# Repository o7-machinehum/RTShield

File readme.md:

# RPI RTShield

The RTSheild is a Raspberry PI hat containing an MCU to serve as a "realtime" companion. The PI is connected to the RP2350 over a UART link, and all sensors are wired into the RP2350 itself. The RP2350 is connected to Arduino compatible headers

## IOs
- 4x Analog output (0-3.3V, 12bit)
- 8x Analog input (0-3.3V, 12bit)
- IO's (3.3V)
- 2x Relays, for dry contacts
- Switches, for config
- LEDs

## Installing
``` bash
git clone https://github.com/o7-machinehum/RTShield
cd RTShield
git submodule update --init --recursive

sudo apt update
sudo apt install -y build-essential cmake ninja-build gcc-arm-none-eabi \
    libnewlib-arm-none-eabi python3-dev python3-pybind11 openocd

sudo raspi-config nonint do_serial_cons 1
sudo raspi-config nonint do_serial_hw 0
sudo usermod -aG dialout "$USER"

make
make flash # This flashes the RP2350

make install

# Reboot once so the serial-console setting and dialout group membership apply.
sudo reboot
```

## Running
The Python API talks to the shield over `/dev/serial0`:

``` python
import rtshield

s = rtshield.Shield("/dev/serial0")
print(s.read_analog_raw(0))
s.write_analog_voltage(0, 1.25)
s.write_digital(2, True)
s.set_led(0, True)
s.set_relay(0, True)
print(s.read_switch(0))
```

## MCU <-> RPI Coms
It's worth mentioning the UART between the MCU and the RPI isn't done very nicely right now. This is to keep things simple. I will eventually do a proper cobs encoding scheme and make things nicer.

## License
The project is licensed under the Creative Commons (4.0 International License) Attribution—Noncommercial—Share Alike license. This allows sharing and adapting material for non-commercial purposes, provided credit is given to the creator and adaptations are shared under the same terms. The material can be used in any format with necessary technical modifications, but no warranties are provided. The license prohibits imposing additional restrictions and ensures the rights are irrevocable as long as the terms are followed.

Basically... If you make boards for yourself: great, make boards for your friends: great, but **please do not sell hundreds on them on Aliexpress**.

Files in `docs/` 3rd party reference material are not covered by this licence.

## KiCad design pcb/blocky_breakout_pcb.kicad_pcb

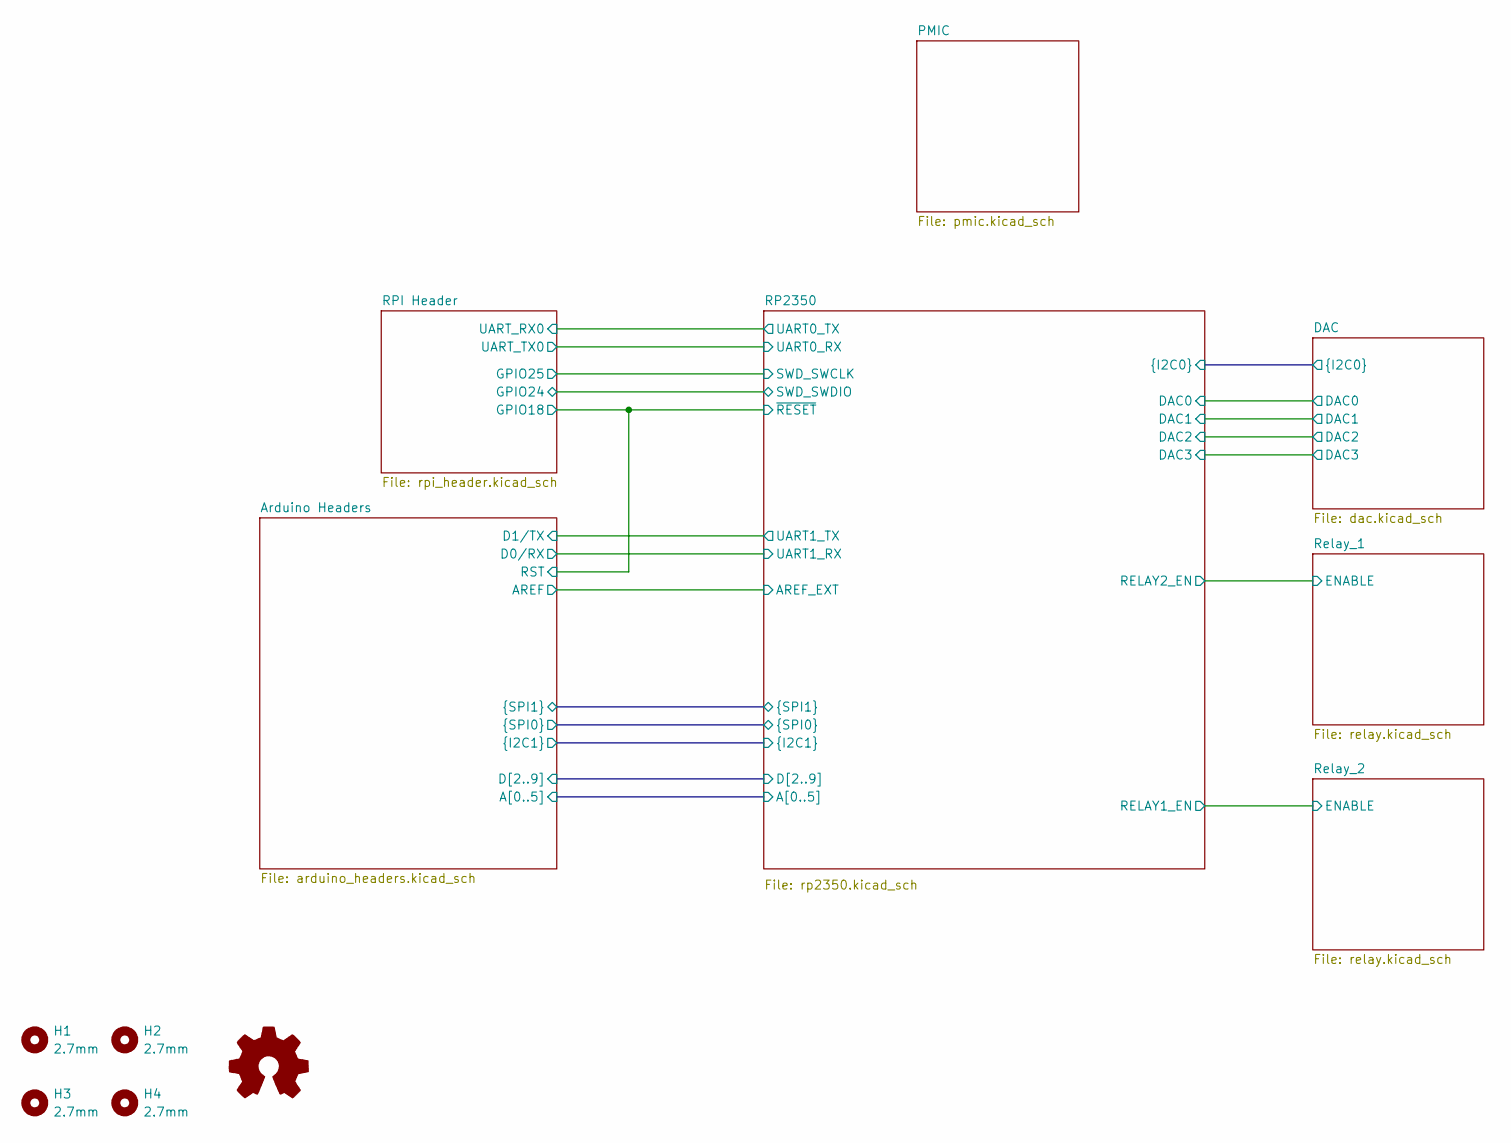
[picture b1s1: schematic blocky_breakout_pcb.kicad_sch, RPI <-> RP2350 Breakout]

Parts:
H1, H2, H3, H4: 2.7mm; MountingHole_2.7mm_M2.5

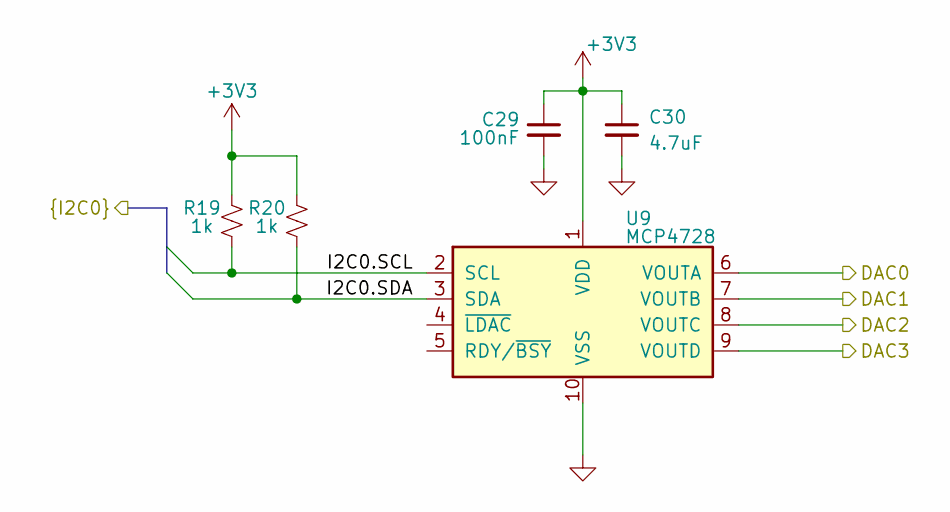
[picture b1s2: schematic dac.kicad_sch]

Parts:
C29: 100nF; C_0402_1005Metric; MPN CL05B104KP5NNNC
C30: 4.7uF; C_0402_1005Metric; MPN JMK105BBJ475MV-F
R19, R20: 1k; R_0402_1005Metric; MPN RC0402FR-131KL
U9: MCP4728; MSOP-10_3x3mm_P0.5mm; MPN MCP4728T-E/UN

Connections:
+3V3: C29.1, C30.1, R19.2, R20.2, U9.1 (VDD); also elsewhere on the board
/DAC/DAC0: U9.6 (VOUTA); also elsewhere on the board
/DAC/DAC1: U9.7 (VOUTB); also elsewhere on the board
/DAC/DAC2: U9.8 (VOUTC); also elsewhere on the board
/DAC/DAC3: U9.9 (VOUTD); also elsewhere on the board
/DAC/I2C0.SCL: R19.1, U9.2 (SCL); also elsewhere on the board
/DAC/I2C0.SDA: R20.1, U9.3 (SDA); also elsewhere on the board
GND: C29.2, C30.2, U9.10 (VSS); also elsewhere on the board

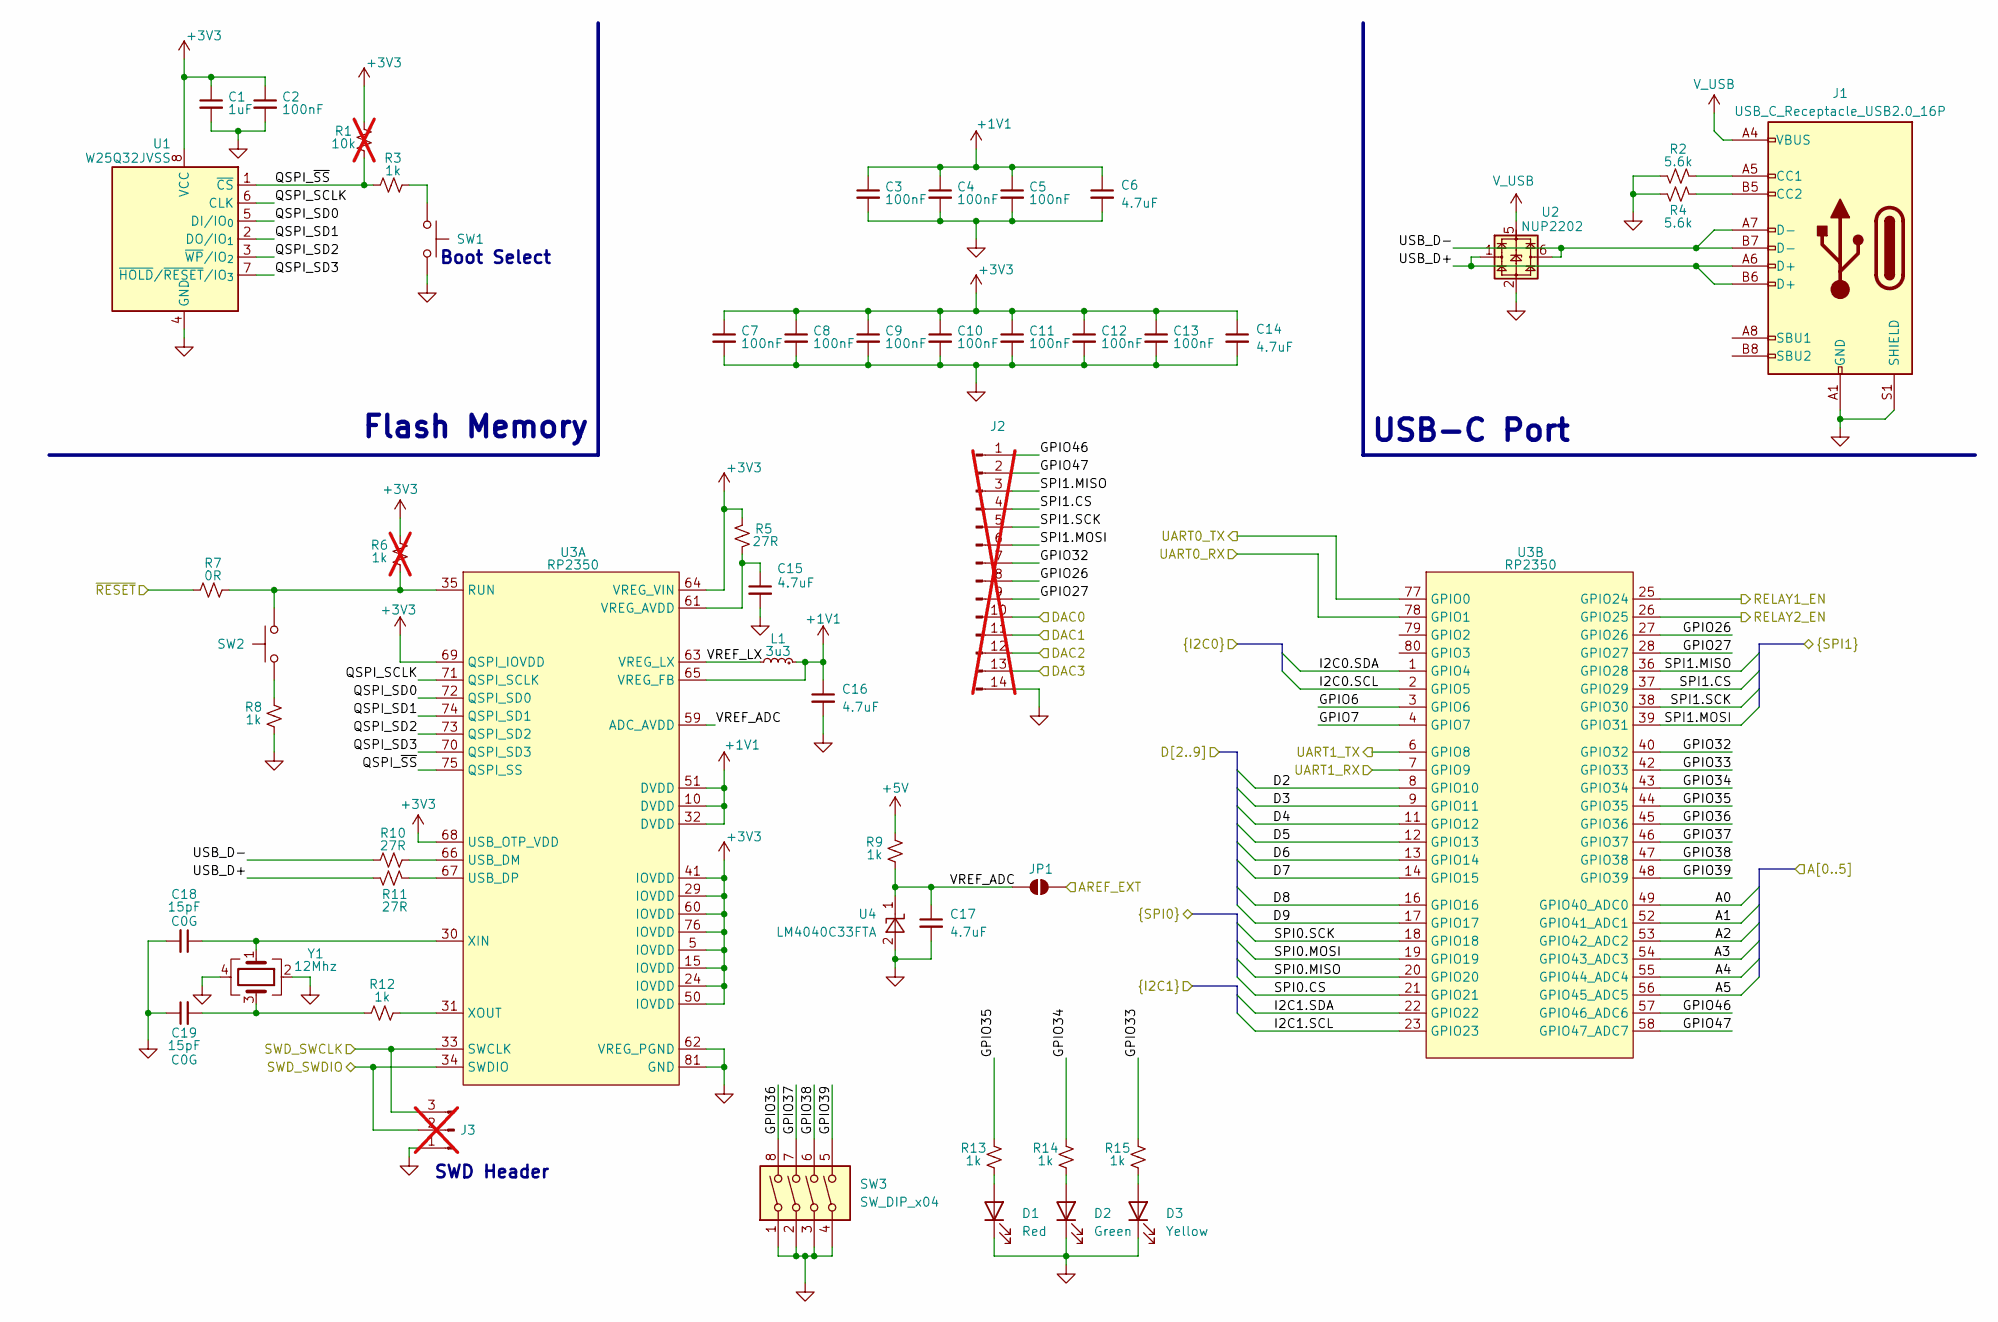
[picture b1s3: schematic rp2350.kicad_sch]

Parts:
C1: 1uF; C_0402_1005Metric; MPN JMK105BJ105KV-F
C2, C3, C4, C5, C7, C8, C9, C10, C11, C12, C13: 100nF; C_0402_1005Metric; MPN CL05B104KP5NNNC
C6, C14, C15, C16, C17: 4.7uF; C_0402_1005Metric; MPN JMK105BBJ475MV-F
C18, C19: 15pF; C_0402_1005Metric; MPN GJM1555C1H150GB01D
D1: Red; LED_0603_1608Metric; MPN LTST-C190KRKT
D2: Green; LED_0603_1608Metric; MPN LTST-C190GKT
D3: Yellow; LED_0603_1608Metric; MPN LTST-C190KSKT
J1: USB_C_Receptacle_USB2.0_16P; USB_C_Receptacle_GCT_USB4105-xx-A_16P_TopMnt_Horizontal; MPN USB4105-GF-A-120
J2: Conn_01x14_Pin; PinHeader_1x14_P2.54mm_Vertical; MPN 77311-101-14LF; not fitted
J3: Conn_01x03_Pin; PinHeader_1x03_P2.54mm_Vertical; not fitted
JP1: SolderJumper_2_Open; SolderJumper-2_P1.3mm_Open_RoundedPad1.0x1.5mm
L1: 3u3; AOTA-B201610S3R3-101-T; MPN AOTA-B201610S3R3-101-T
R1: 10k; R_0402_1005Metric; MPN RC0402FR-1310KL; not fitted
R2, R4: 5.6k; R_0402_1005Metric; MPN RC0402FR-135K6L
R3, R8, R9, R12, R13, R14, R15: 1k; R_0402_1005Metric; MPN RC0402FR-131KL
R5, R10, R11: 27R; R_0402_1005Metric; MPN RC0402FR-1327RL
R6: 1k; R_0402_1005Metric; MPN RC0402FR-131KL; not fitted
R7: 0R; R_0402_1005Metric; MPN RC0402FR-070RL
SW1, SW2: SW_Push; SW_SPST_PTS647_Sx38; MPN PTS647SK38SMTR2 LFS
SW3: SW_DIP_x04; SW_DIP_SPSTx04_Slide_Omron_A6S-410x_W8.9mm_P2.54mm; MPN A6S-4102-PH
U1: W25Q32JVSS; SOIC-8_5.3x5.3mm_P1.27mm; MPN W25Q32JVSSIQ
U2: NUP2202; SOT-363_SC-70-6; MPN NUP2202W1T2G
U3: RP2350; QFN-80-1EP_10x10mm_P0.4mm_EP3.4x3.4mm; MPN RP2350B
U4: LM4040C33FTA; SOT-23; MPN LM4040C33FTA
Y1: 12Mhz; Crystal_SMD_Abracon_ABM8-272-T3-4Pin_3.2x2.5mm; MPN ABM8-272-T3

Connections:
+1V1: C3.1, C4.1, C5.1, C6.1, C16.1, L1.1, U3.10 (DVDD), U3.32 (DVDD), U3.51 (DVDD), U3.65 (VREG_FB); also elsewhere on the board
+3V3: C1.1, C2.1, C7.1, C8.1, C9.1, C10.1, C11.1, C12.1, C13.1, C14.1, R1.2, R5.2, R6.2, U1.8 (VCC), U3.5 (IOVDD), U3.15 (IOVDD), U3.24 (IOVDD), U3.29 (IOVDD), U3.41 (IOVDD), U3.50 (IOVDD), U3.60 (IOVDD), U3.64 (VREG_VIN), U3.68 (USB_OTP_VDD), U3.69 (QSPI_IOVDD), U3.76 (IOVDD); also elsewhere on the board
+5V: R9.2; also elsewhere on the board
/Arduino Headers/A0: U3.49 (GPIO40_ADC0); also elsewhere on the board
/Arduino Headers/A1: U3.52 (GPIO41_ADC1); also elsewhere on the board
/Arduino Headers/A2: U3.53 (GPIO42_ADC2); also elsewhere on the board
/Arduino Headers/A3: U3.54 (GPIO43_ADC3); also elsewhere on the board
/Arduino Headers/A4: U3.55 (GPIO44_ADC4); also elsewhere on the board
/Arduino Headers/A5: U3.56 (GPIO45_ADC5); also elsewhere on the board
/Arduino Headers/AREF: JP1.2 (B); also elsewhere on the board
/Arduino Headers/D0/RX: U3.7 (GPIO9); also elsewhere on the board
/Arduino Headers/D1/TX: U3.6 (GPIO8); also elsewhere on the board
/Arduino Headers/D2: U3.8 (GPIO10); also elsewhere on the board
/Arduino Headers/D3: U3.9 (GPIO11); also elsewhere on the board
/Arduino Headers/D4: U3.11 (GPIO12); also elsewhere on the board
/Arduino Headers/D5: U3.12 (GPIO13); also elsewhere on the board
/Arduino Headers/D6: U3.13 (GPIO14); also elsewhere on the board
/Arduino Headers/D7: U3.14 (GPIO15); also elsewhere on the board
/Arduino Headers/D8: U3.16 (GPIO16); also elsewhere on the board
/Arduino Headers/D9: U3.17 (GPIO17); also elsewhere on the board
/Arduino Headers/I2C1.SCL: U3.23 (GPIO23); also elsewhere on the board
/Arduino Headers/I2C1.SDA: U3.22 (GPIO22); also elsewhere on the board
/Arduino Headers/RST: R7.1; also elsewhere on the board
/Arduino Headers/SPI0.CS: U3.21 (GPIO21); also elsewhere on the board
/Arduino Headers/SPI0.MISO: U3.20 (GPIO20); also elsewhere on the board
/Arduino Headers/SPI0.MOSI: U3.19 (GPIO19); also elsewhere on the board
/Arduino Headers/SPI0.SCK: U3.18 (GPIO18); also elsewhere on the board
/Arduino Headers/SPI1.CS: J2.4, U3.37 (GPIO29)
/Arduino Headers/SPI1.MISO: J2.3, U3.36 (GPIO28); also elsewhere on the board
/Arduino Headers/SPI1.MOSI: J2.6, U3.39 (GPIO31); also elsewhere on the board
/Arduino Headers/SPI1.SCK: J2.5, U3.38 (GPIO30); also elsewhere on the board
/DAC/DAC0: J2.10; also elsewhere on the board
/DAC/DAC1: J2.11; also elsewhere on the board
/DAC/DAC2: J2.12; also elsewhere on the board
/DAC/DAC3: J2.13; also elsewhere on the board
/DAC/I2C0.SCL: U3.2 (GPIO5); also elsewhere on the board
/DAC/I2C0.SDA: U3.1 (GPIO4); also elsewhere on the board
/RP2350/GPIO6: U3.3 (GPIO6)
/RP2350/GPIO7: U3.4 (GPIO7)
/RP2350/GPIO26: J2.8, U3.27 (GPIO26)
/RP2350/GPIO27: J2.9, U3.28 (GPIO27)
/RP2350/GPIO32: J2.7, U3.40 (GPIO32)
/RP2350/GPIO33: R15.2, U3.42 (GPIO33)
/RP2350/GPIO34: R14.2, U3.43 (GPIO34)
/RP2350/GPIO35: R13.2, U3.44 (GPIO35)
/RP2350/GPIO36: SW3.8, U3.45 (GPIO36)
/RP2350/GPIO37: SW3.7, U3.46 (GPIO37)
/RP2350/GPIO38: SW3.6, U3.47 (GPIO38)
/RP2350/GPIO39: SW3.5, U3.48 (GPIO39)
/RP2350/GPIO46: J2.1, U3.57 (GPIO46_ADC6)
/RP2350/GPIO47: J2.2, U3.58 (GPIO47_ADC7)
/RP2350/QSPI_SCLK: U1.6 (CLK), U3.71 (QSPI_SCLK)
/RP2350/QSPI_SD0: U1.5 (DI/IO_{0}), U3.72 (QSPI_SD0)
/RP2350/QSPI_SD1: U1.2 (DO/IO_{1}), U3.74 (QSPI_SD1)
/RP2350/QSPI_SD2: U1.3 (~WP/IO_{2}), U3.73 (QSPI_SD2)
/RP2350/QSPI_SD3: U1.7 (~HOLD/~RESET/IO_{3}), U3.70 (QSPI_SD3)
/RP2350/QSPI_~SS: R1.1, R3.1, U1.1 (~CS), U3.75 (QSPI_SS)
/RP2350/RELAY1_EN: U3.25 (GPIO24); also elsewhere on the board
/RP2350/RELAY2_EN: U3.26 (GPIO25); also elsewhere on the board
/RP2350/SWD_SWCLK: J3.3, U3.33 (SWCLK); also elsewhere on the board
/RP2350/SWD_SWDIO: J3.2, U3.34 (SWDIO); also elsewhere on the board
/RP2350/UART0_RX: U3.78 (GPIO1); also elsewhere on the board
/RP2350/UART0_TX: U3.77 (GPIO0); also elsewhere on the board
/RP2350/USB_D+: J1.A6 (D+), J1.B6 (D+), R11.1, U2.1
/RP2350/USB_D-: J1.A7 (D-), J1.B7 (D-), R10.1, U2.6
/RP2350/VREF_ADC: C17.1, JP1.1 (A), R9.1, U3.59 (ADC_AVDD), U4.1 (K)
/RP2350/VREF_LX: L1.2, U3.63 (VREG_LX)
GND: C1.2, C2.2, C3.2, C4.2, C5.2, C6.2, C7.2, C8.2, C9.2, C10.2, C11.2, C12.2, C13.2, C14.2, C15.2, C16.2, C17.2, C18.2, C19.1, D1.1 (K), D2.1 (K), D3.1 (K), J1.A1 (GND), J1.A12 (GND), J1.B1 (GND), J1.B12 (GND), J1.S1 (SHIELD), J2.14, J3.1, R2.2, R4.1, R8.1, SW1.2, SW3.1, SW3.2, SW3.3, SW3.4, U1.4 (GND), U2.2, U3.62 (VREG_PGND), U3.81 (GND), U4.2 (A), Y1.2, Y1.4; also elsewhere on the board
unnamed: C19.2, R12.1, Y1.3
unnamed: D1.2 (A), R13.1
unnamed: D2.2 (A), R14.1
unnamed: D3.2 (A), R15.1
unnamed: J1.A5 (CC1), R2.1
unnamed: J1.B5 (CC2), R4.2
unnamed: R3.2, SW1.1
unnamed: R8.2, SW2.1
unnamed: R6.1, R7.2, SW2.2, U3.35 (RUN)
unnamed: R10.2, U3.66 (USB_DM)
unnamed: R11.2, U3.67 (USB_DP)
unnamed: C15.1, R5.1, U3.61 (VREG_AVDD)
unnamed: C18.1, U3.30 (XIN), Y1.1
unnamed: R12.2, U3.31 (XOUT)
V_USB: J1.A4 (VBUS), J1.A9 (VBUS), J1.B4 (VBUS), J1.B9 (VBUS), U2.5; also elsewhere on the board

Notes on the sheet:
SWD Header
Flash Memory
Boot Select
USB-C Port

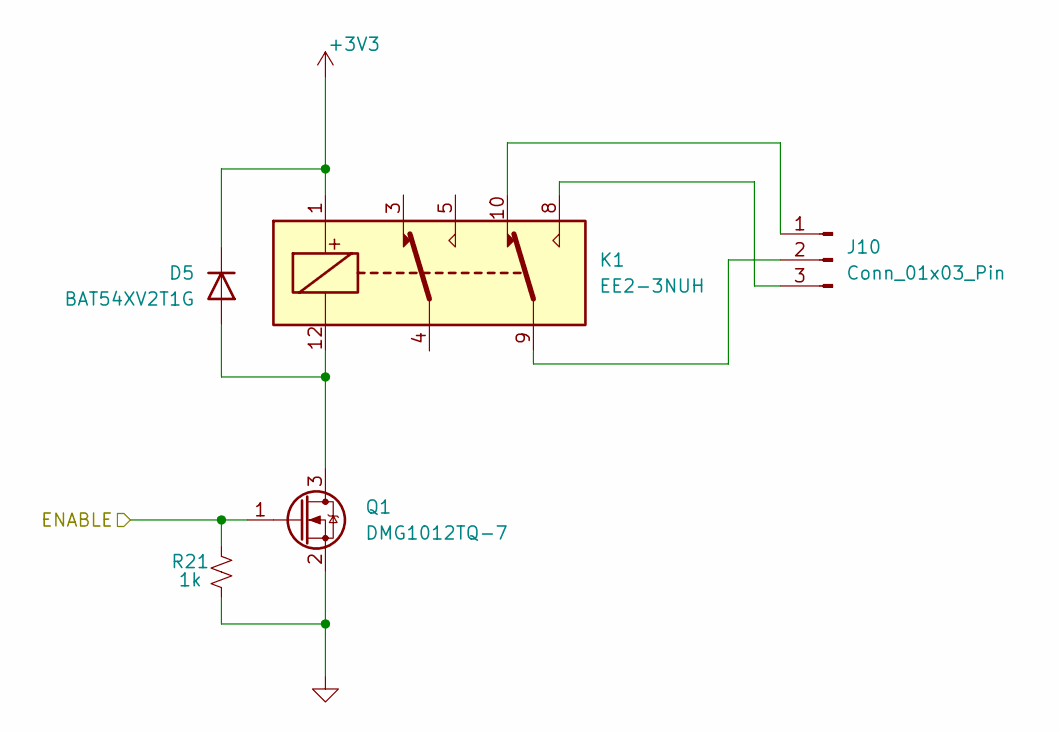
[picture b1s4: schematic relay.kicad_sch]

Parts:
D5: BAT54XV2T1G; D_SOD-523; MPN BAT54XV2T1G
J10: Conn_01x03_Pin; JST_XH_S3B-XH-A-1_1x03_P2.50mm_Horizontal; MPN S3B-XH-A-1
K1: EE2-3NUH; Relay_DPDT_Kemet_EE2_NUH
Q1: DMG1012TQ-7; SOT-523; MPN DMG1012TQ-7
R21: 1k; R_0402_1005Metric; MPN RC0402FR-131KL

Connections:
+3V3: D5.1 (K), K1.1; also elsewhere on the board
/RP2350/RELAY2_EN: Q1.1 (G), R21.1; also elsewhere on the board
GND: Q1.2 (S), R21.2; also elsewhere on the board
unnamed: D5.2 (A), K1.12, Q1.3 (D)
unnamed: J10.1, K1.10
unnamed: J10.2, K1.9
unnamed: J10.3, K1.8

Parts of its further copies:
D6: BAT54XV2T1G; D_SOD-523; MPN BAT54XV2T1G
J11: Conn_01x03_Pin; JST_XH_S3B-XH-A-1_1x03_P2.50mm_Horizontal; MPN S3B-XH-A-1
Q2: DMG1012TQ-7; SOT-523; MPN DMG1012TQ-7
R22: 1k; R_0402_1005Metric; MPN RC0402FR-131KL

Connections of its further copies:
+3V3: D6.1 (K); also elsewhere on the board
/RP2350/RELAY1_EN: Q2.1 (G), R22.1; also elsewhere on the board
GND: Q2.2 (S), R22.2; also elsewhere on the board
unnamed 75: D6.2 (A), Q2.3 (D); also elsewhere on the board
unnamed 81: J11.1; also elsewhere on the board
unnamed 82: J11.2; also elsewhere on the board
unnamed 83: J11.3; also elsewhere on the board

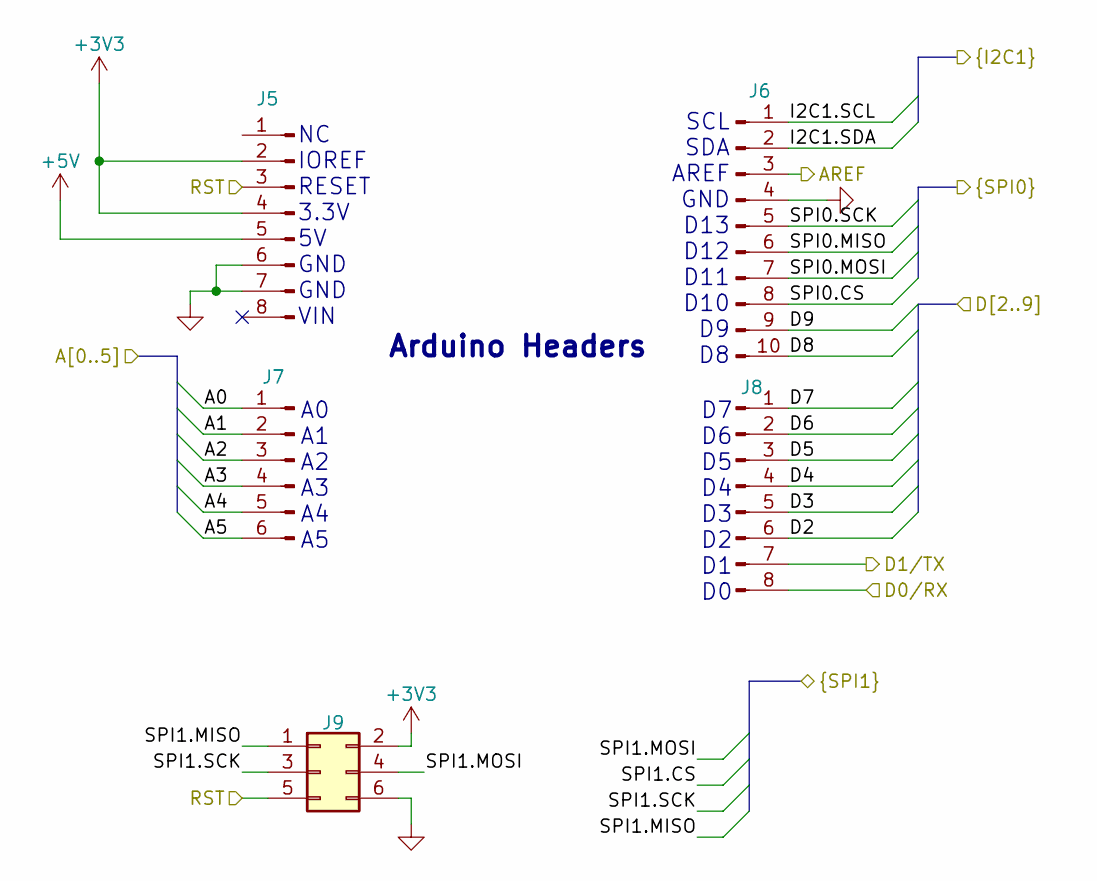
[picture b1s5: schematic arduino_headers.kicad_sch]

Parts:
J5, J8: Conn_01x08_Pin; PinSocket_1x08_P2.54mm_Vertical_SMD_Pin1Left; MPN NPTC081KFXC-RC
J6: Conn_01x10_Pin; PinSocket_1x10_P2.54mm_Vertical_SMD_Pin1Left; MPN NPTC101KFXC-RC
J7: Conn_01x06_Pin; PinSocket_1x06_P2.54mm_Vertical_SMD_Pin1Left; MPN NPTC061KFXC-RC
J9: Conn_02x03_Odd_Even; PinHeader_2x03_P2.54mm_Vertical; MPN 67997-206HLF

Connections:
+3V3: J5.2, J5.4, J9.2; also elsewhere on the board
+5V: J5.5; also elsewhere on the board
/Arduino Headers/A0: J7.1; also elsewhere on the board
/Arduino Headers/A1: J7.2; also elsewhere on the board
/Arduino Headers/A2: J7.3; also elsewhere on the board
/Arduino Headers/A3: J7.4; also elsewhere on the board
/Arduino Headers/A4: J7.5; also elsewhere on the board
/Arduino Headers/A5: J7.6; also elsewhere on the board
/Arduino Headers/AREF: J6.3; also elsewhere on the board
/Arduino Headers/D0/RX: J8.8; also elsewhere on the board
/Arduino Headers/D1/TX: J8.7; also elsewhere on the board
/Arduino Headers/D2: J8.6; also elsewhere on the board
/Arduino Headers/D3: J8.5; also elsewhere on the board
/Arduino Headers/D4: J8.4; also elsewhere on the board
/Arduino Headers/D5: J8.3; also elsewhere on the board
/Arduino Headers/D6: J8.2; also elsewhere on the board
/Arduino Headers/D7: J8.1; also elsewhere on the board
/Arduino Headers/D8: J6.10; also elsewhere on the board
/Arduino Headers/D9: J6.9; also elsewhere on the board
/Arduino Headers/I2C1.SCL: J6.1; also elsewhere on the board
/Arduino Headers/I2C1.SDA: J6.2; also elsewhere on the board
/Arduino Headers/RST: J5.3, J9.5; also elsewhere on the board
/Arduino Headers/SPI0.CS: J6.8; also elsewhere on the board
/Arduino Headers/SPI0.MISO: J6.6; also elsewhere on the board
/Arduino Headers/SPI0.MOSI: J6.7; also elsewhere on the board
/Arduino Headers/SPI0.SCK: J6.5; also elsewhere on the board
/Arduino Headers/SPI1.MISO: J9.1; also elsewhere on the board
/Arduino Headers/SPI1.MOSI: J9.4; also elsewhere on the board
/Arduino Headers/SPI1.SCK: J9.3; also elsewhere on the board
GND: J5.6, J5.7, J6.4, J9.6; also elsewhere on the board

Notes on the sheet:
NC IOREF RESET 3.3V 5V GND GND VIN
D7 D6 D5 D4 D3 D2 D1 D0
SCL SDA AREF GND D13 D12 D11 D10 D9 D8
Arduino Headers
A0 A1 A2 A3 A4 A5

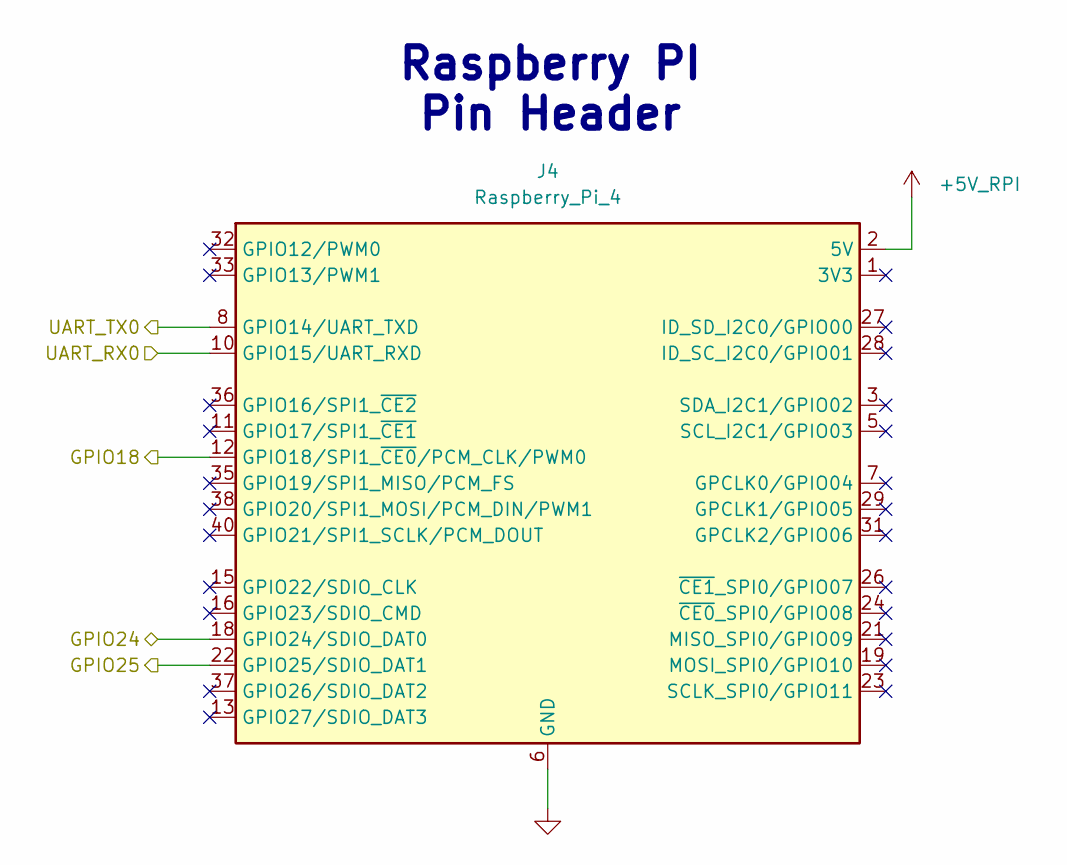
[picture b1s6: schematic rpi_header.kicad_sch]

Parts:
J4: Raspberry_Pi_4; PinSocket_2x20_P2.54mm_Vertical_SMD; MPN NPTC202KFMS-RC

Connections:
+5V_RPI: J4.2 (5V), J4.4 (5V); also elsewhere on the board
/Arduino Headers/RST: J4.12 (GPIO18/SPI1_~CE0/PCM_CLK/PWM0); also elsewhere on the board
/RP2350/SWD_SWCLK: J4.22 (GPIO25/SDIO_DAT1); also elsewhere on the board
/RP2350/SWD_SWDIO: J4.18 (GPIO24/SDIO_DAT0); also elsewhere on the board
/RP2350/UART0_RX: J4.8 (GPIO14/UART_TXD); also elsewhere on the board
/RP2350/UART0_TX: J4.10 (GPIO15/UART_RXD); also elsewhere on the board
GND: J4.6 (GND), J4.9 (GND), J4.14 (GND), J4.20 (GND), J4.25 (GND), J4.30 (GND), J4.34 (GND), J4.39 (GND); also elsewhere on the board

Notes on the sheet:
Raspberry PI Pin Header

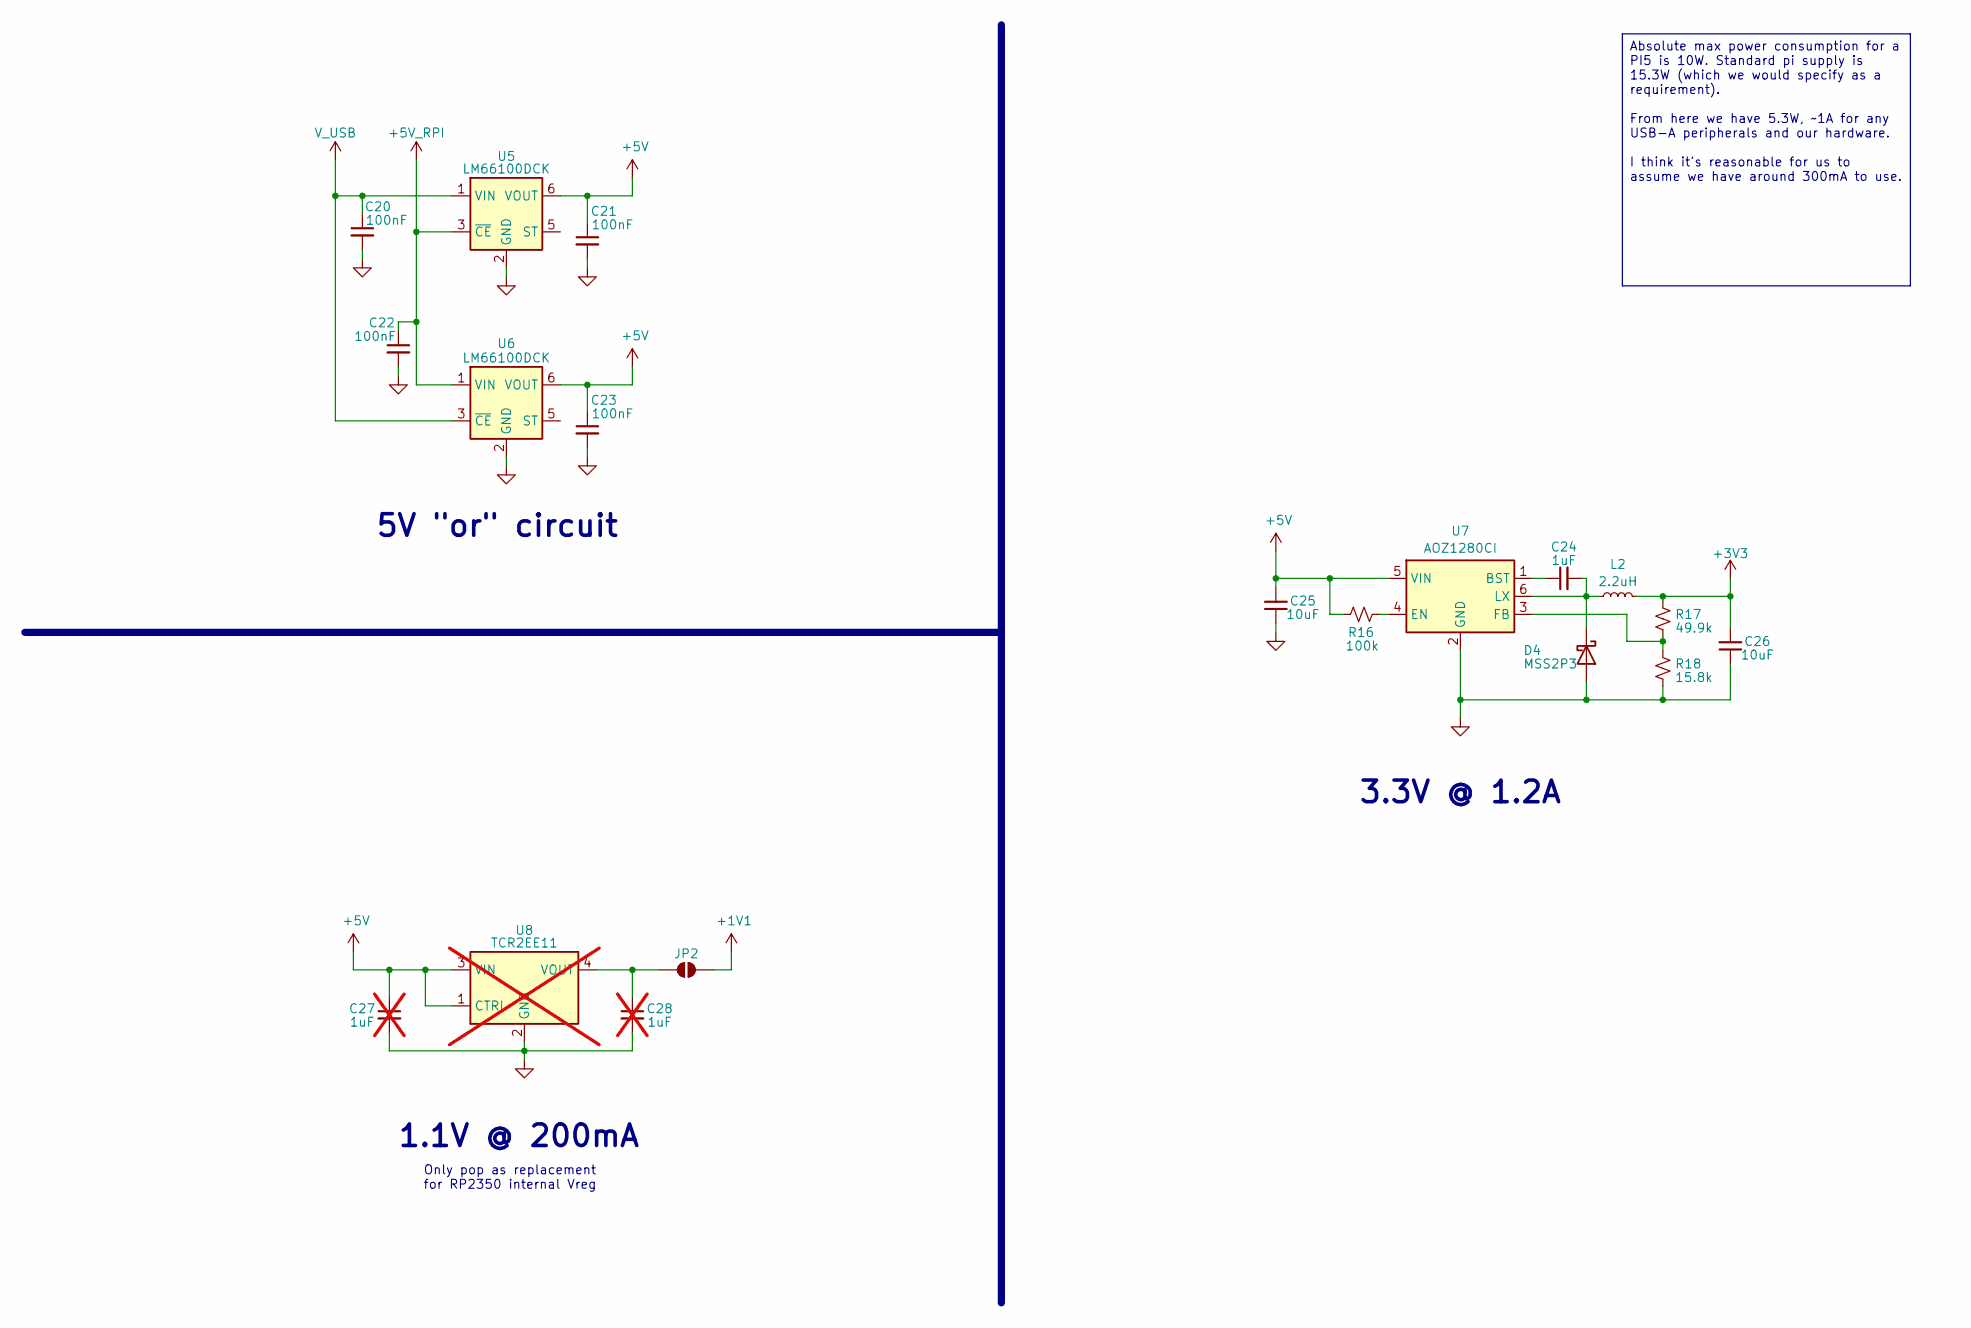
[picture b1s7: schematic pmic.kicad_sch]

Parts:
C20, C21, C22, C23: 100nF; C_0402_1005Metric; MPN CL05B104KP5NNNC
C24: 1uF; C_0402_1005Metric; MPN JMK105BJ105KV-F
C25, C26: 10uF; C_0603_1608Metric; MPN GRM188R61E106KA73J
C27, C28: 1uF; C_0402_1005Metric; MPN JMK105BJ105KV-F; not fitted
D4: MSS2P3; D_MicroSMP_AK; MPN MSS2P3-M3/89A
JP2: SolderJumper_2_Open; SolderJumper-2_P1.3mm_Open_RoundedPad1.0x1.5mm
L2: 2.2uH; L_1008_2520Metric; MPN DFE252012P-2R2M=P2
R16: 100k; R_0402_1005Metric; MPN RC0402FR-13100KL
R17: 49.9k; R_0402_1005Metric; MPN RC0402FR-1349K9L
R18: 15.8k; R_0402_1005Metric; MPN RC0402FR-1315K8L
U5, U6: LM66100DCK; SOT-363_SC-70-6; MPN LM66100DCKR
U7: AOZ1280CI; SOT-23-6; MPN AOZ1280CI
U8: TCR2EE11; SOT-553; MPN TCR2EE11,LM(CT; not fitted

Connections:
+1V1: JP2.2 (B); also elsewhere on the board
+3V3: C26.2, L2.2, R17.2; also elsewhere on the board
+5V: C21.1, C23.1, C25.2, C27.1, R16.1, U5.6 (VOUT), U6.6 (VOUT), U7.5 (VIN), U8.1 (CTRL), U8.3 (VIN); also elsewhere on the board
+5V_RPI: C22.1, U5.3 (~CE), U6.1 (VIN); also elsewhere on the board
GND: C20.2, C21.2, C22.2, C23.2, C25.1, C26.1, C27.2, C28.2, D4.2 (A), R18.1, U5.2 (GND), U6.2 (GND), U7.2 (GND), U8.2 (GND); also elsewhere on the board
unnamed: C24.2, D4.1 (K), L2.1, U7.6 (LX)
unnamed: C28.1, JP2.1 (A), U8.4 (VOUT)
unnamed: C24.1, U7.1 (BST)
unnamed: R16.2, U7.4 (EN)
unnamed: R17.1, R18.2, U7.3 (FB)
V_USB: C20.1, U5.1 (VIN), U6.3 (~CE); also elsewhere on the board

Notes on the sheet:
1.1V @ 200mA
5V "or" circuit
Only pop as replacement for RP2350 internal Vreg
3.3V @ 1.2A
Absolute max power consumption for a PI5 is 10W. Standard pi supply is 15.3W (which we would specify as a requirement). From here we have 5.3W, ~1A for any USB-A peripherals and our hardware. I think it's reasonable for us to assume we have around 300mA to use.

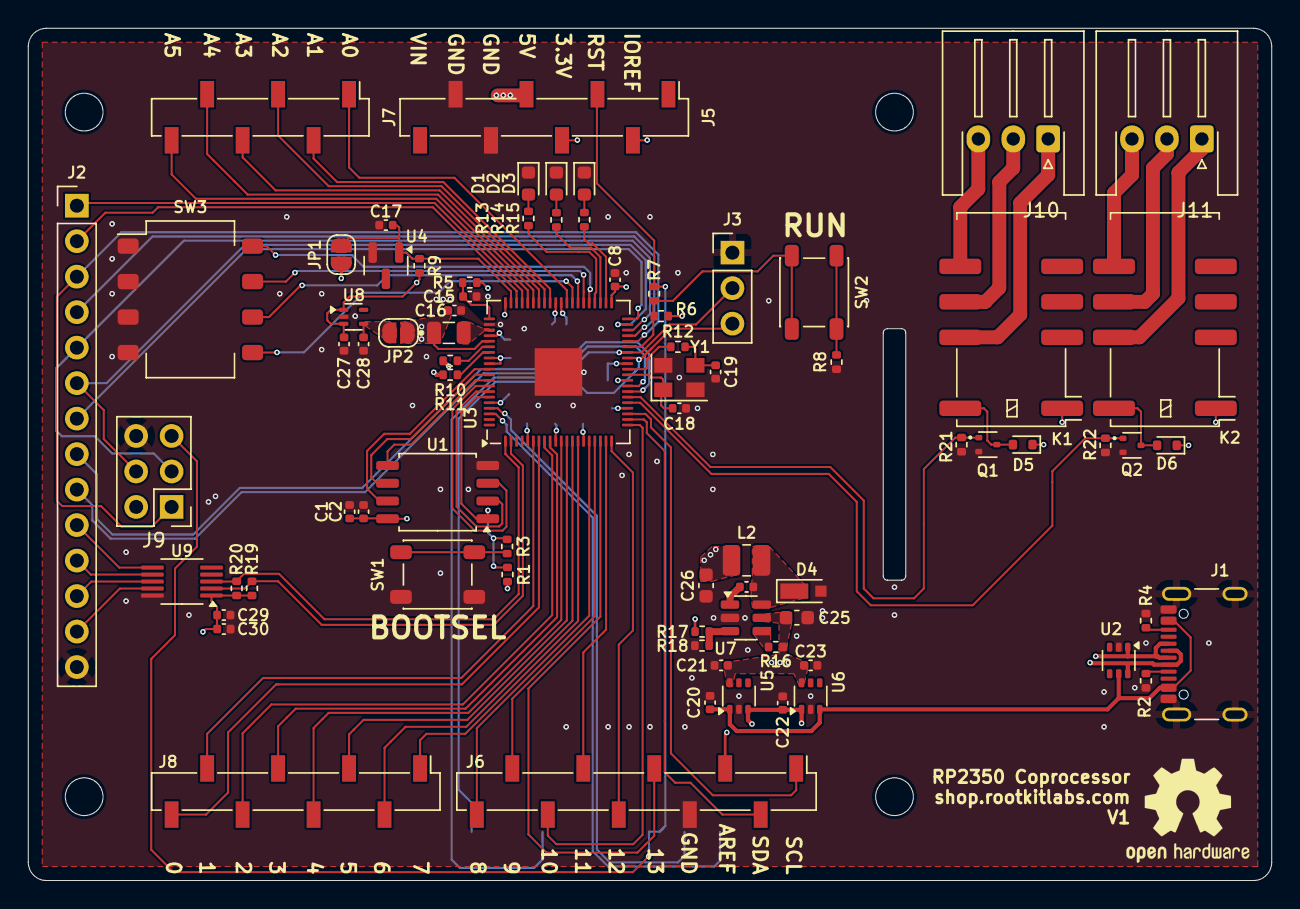
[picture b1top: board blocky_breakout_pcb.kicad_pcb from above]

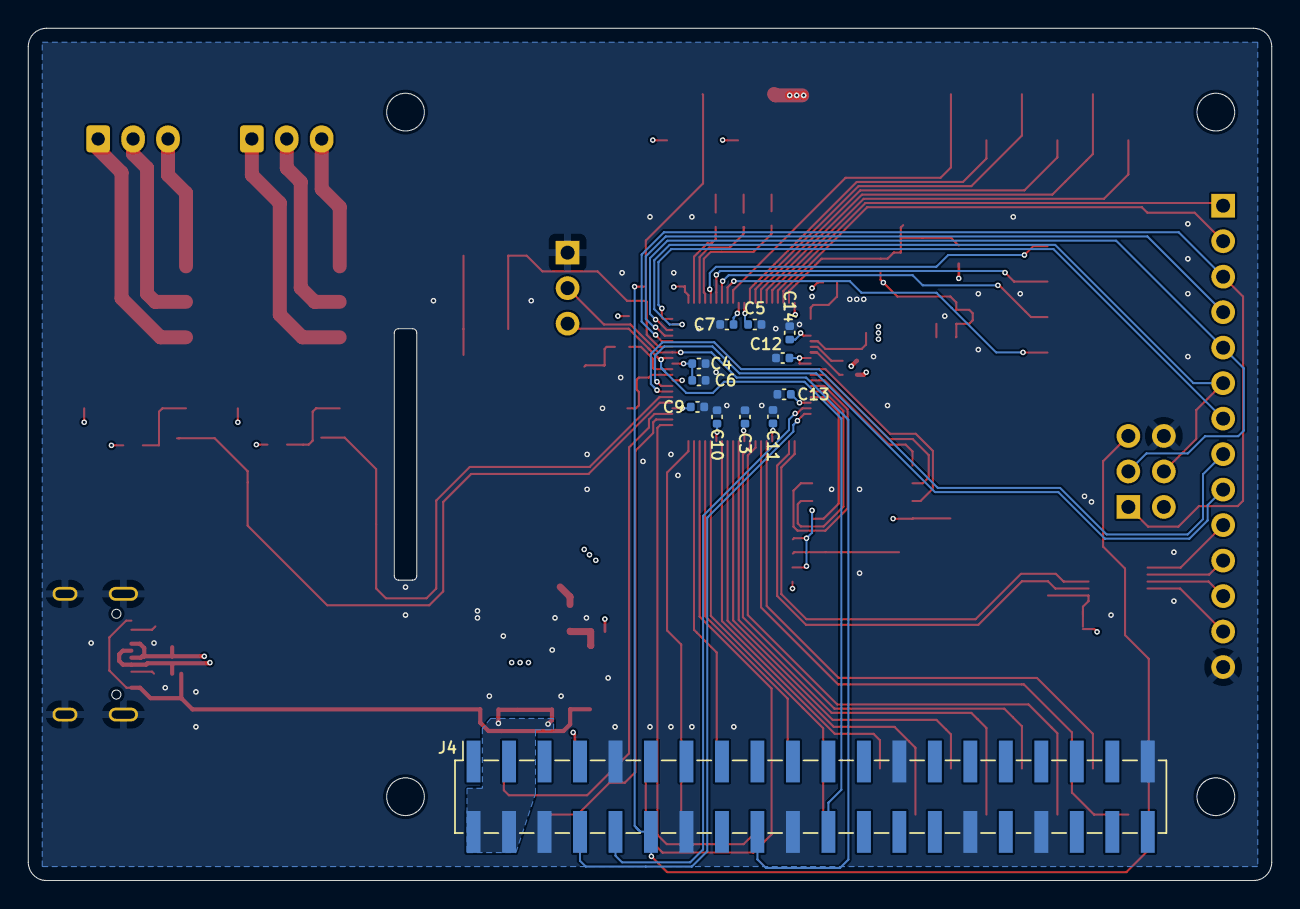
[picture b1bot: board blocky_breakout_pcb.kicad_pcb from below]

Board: 4 copper layers, 89.0 x 61.0 mm, 94 parts (16 on the bottom side), 95 nets.

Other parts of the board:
K2: EE2-3TNUH; Relay_DPDT_Kemet_EE2_NU

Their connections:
+3V3: K2.1; also elsewhere on the board
unnamed 75: K2.12; also elsewhere on the board
unnamed 81: K2.10; also elsewhere on the board
unnamed 82: K2.9; also elsewhere on the board
unnamed 83: K2.8; also elsewhere on the board

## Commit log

2025-08-07 init
2025-08-14 Layout nearly finished, entering part numbers
2025-08-19 Added some docs, worked on routing.
2025-08-19 Renamed
2025-08-19 Added gerbers, added 2x3 Arduino header.
2025-08-20 Added remaining part numbers, removed silk for holes, minor touchups
2025-09-02 R0.1 released
2025-09-24 R0.1 updated
2025-09-24 Added release script
2026-05-27 Readme + image
2026-05-28 Intial firmware commit.
2026-05-28 Added a few more details.
2026-05-28 Made a board specific defn' file, added some more setup instructions in the readme.
